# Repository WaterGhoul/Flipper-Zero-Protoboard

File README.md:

# Flipper-Zero-Protoboard
A basic protoboard for the Flipper Zero with LED power indicators

# Purchasing
You can purchase this and my other products on Tindie!

# Donate
Nothing is EVER expected for providing my designs, however if you wish to support my work, you may donate to these addresses.

**ETH** ``0x7C65625d6dac7DC351eEf3C0A21e9f0F4a3B537b``

**BTC** ``bc1q4rn3ceyk42349uuxt2m7mzw4kcewu0e5698fms``

**DOGE** ``DC1Q4ip8mLsAgvbLL4evxJQhaCE7QosFZ9``

**LTC** ``ltc1q33sg6eea2yqzdx85h38v7rpw7kzlgmqtn8m5nm``

# License
<br />This work is licensed under a <a rel="license" href="http://creativecommons.org/licenses/by-sa/4.0/">Creative Commons Attribution-ShareAlike 4.0 International License</a>.

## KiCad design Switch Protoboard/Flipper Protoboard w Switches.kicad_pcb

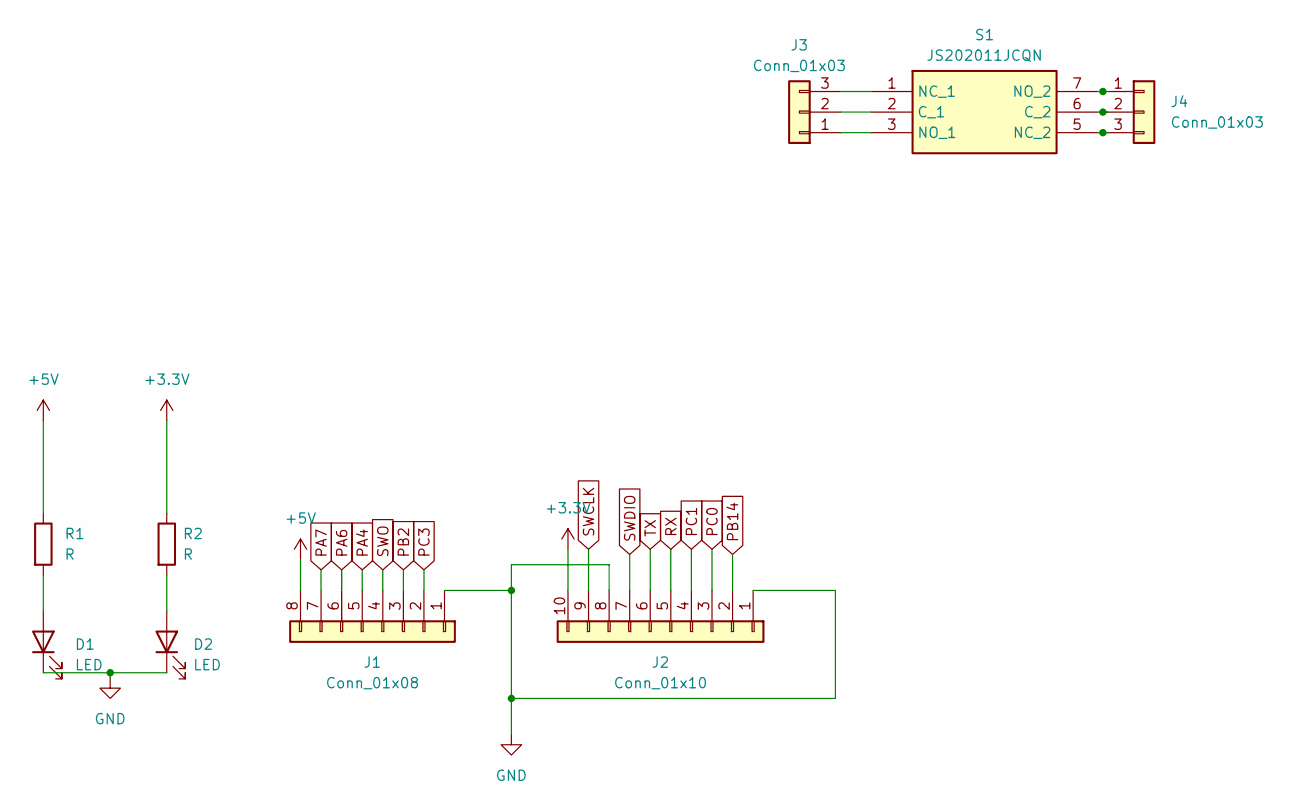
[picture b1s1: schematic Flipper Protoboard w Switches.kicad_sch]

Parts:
D1, D2: LED; LED_0603_1608Metric
J1: Conn_01x08; PinHeader_1x08_P2.54mm_Horizontal
J2: Conn_01x10; PinHeader_1x10_P2.54mm_Horizontal
J3, J4: Conn_01x03; PinHeader_1x03_P2.54mm_Vertical
R1, R2: R; R_0603_1608Metric
S1: JS202011JCQN; Mouser Part Number 611-JS202011JCQN

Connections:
+3.3V: J2.10, R2.1
+5V: J1.8, R1.1
GND: D1.1 (K), D2.1 (K), J1.1, J2.1, J2.8
unnamed: D1.2 (A), R1.2
unnamed: D2.2 (A), R2.2
unnamed: J3.1, S1.3 (NO_1)
unnamed: J3.2, S1.2 (C_1)
unnamed: J3.3, S1.1 (NC_1)
unnamed: J4.1, S1.7 (NO_2)
unnamed: J4.2, S1.6 (C_2)
unnamed: J4.3, S1.5 (NC_2)
PA4: J1.5
PA6: J1.6
PA7: J1.7
PB2: J1.3
PB14: J2.2
PC0: J2.3
PC1: J2.4
PC3: J1.2
RX: J2.5
SWCLK: J2.9
SWDIO: J2.7
SWO: J1.4
TX: J2.6

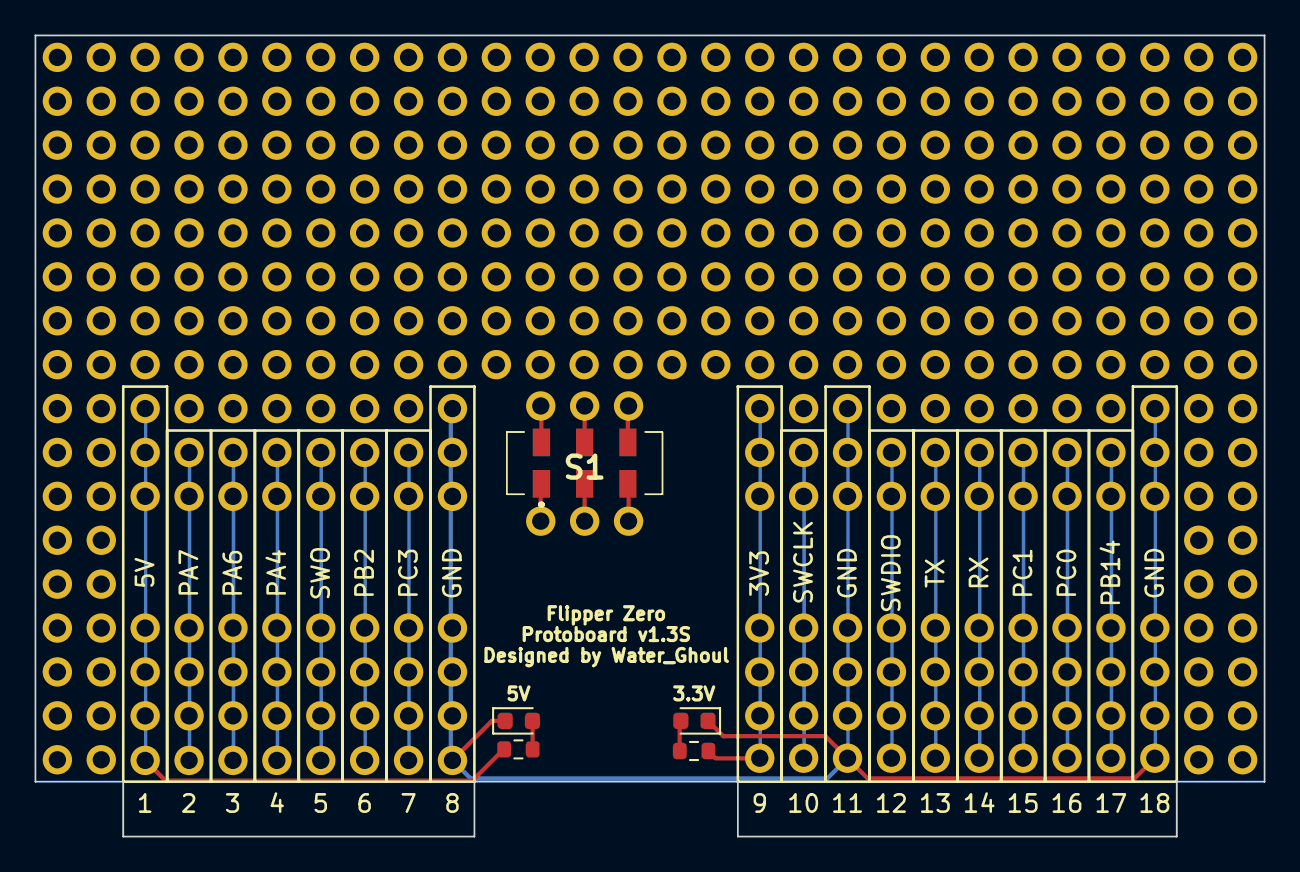
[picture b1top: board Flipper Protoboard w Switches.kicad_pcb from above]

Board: 2 copper layers, 71.1 x 46.4 mm, 377 parts (0 on the bottom side), 11 nets.

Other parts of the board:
REF1, REF1#2, REF2, REF3, REF4, REF5, REF6, REF7, REF8, REF9, REF10, REF11, REF12, REF13, REF14, REF15, REF16, REF17, REF18, REF19, REF20, REF21, REF22, REF23, REF24, REF24#2, REF25, REF26, REF27, REF28, REF29, REF30, REF31, REF32, REF33, REF34, REF35, REF36, REF37, REF38, REF39, REF40, REF41, REF42, REF43, REF44, REF45, REF46, REF47, REF48, REF49, REF50, REF51, REF52, REF53, REF54, REF55, REF56, REF57, REF58, REF59, REF60, REF61, REF62, REF63, REF64, REF65, REF66, REF67, REF68, REF69, REF70, REF71, REF72, REF73, REF74, REF75, REF76, REF77, REF78, REF79, REF80, REF81, REF82, REF83, REF84, REF85, REF86, REF87, REF88, REF89, REF90, REF91, REF92, REF93, REF94, REF95, REF96, REF97, REF98, REF99, REF100, REF101, REF102, REF103, REF104, REF105, REF106, REF107, REF108, REF109, REF110, REF111, REF112, REF113, REF114, REF115, REF116, REF117, REF118, REF119, REF120, REF121, REF121#2, REF122, REF122#2, REF123, REF123#2, REF124, REF124#2, REF125, REF125#2, REF126, REF126#2, REF127, REF127#2, REF128, REF128#2, REF129, REF130, REF131, REF132, REF133, REF134, REF135, REF136, REF137, REF138, REF139, REF140, REF141, REF142, REF143, REF144, REF145, REF146, REF147, REF148, REF149, REF150, REF151, REF152, REF153, REF154, REF155, REF156, REF157, REF158, REF159, REF160, REF161, REF162, REF163, REF164, REF165, REF166, REF167, REF168, REF169, REF169#2, REF170, REF170#2, REF171, REF171#2, REF172, REF172#2, REF173, REF173#2, REF174, REF174#2, REF175, REF175#2, REF176, REF176#2, REF177, REF178, REF179, REF180, REF181, REF182, REF183, REF183#2, REF183#3, REF184, REF184#2, REF184#3, REF185, REF185#2, REF185#3, REF186, REF186#2, REF186#3, REF187, REF187#2, REF187#3, REF188, REF188#2, REF188#3, REF189, REF189#2, REF189#3, REF190, REF190#2, REF190#3, REF191, REF191#2, REF191#3, REF192, REF192#2, REF192#3, REF193, REF194, REF195, REF196, REF197, REF198, REF199, REF200, REF207, REF208, REF209, REF210, REF211, REF212, REF213, REF214, REF215, REF216, REF217, REF218, REF219, REF220, REF221, REF222, REF223, REF224, REF231, REF232, REF233, REF234, REF235, REF236, REF237, REF238, REF239, REF240, REF240#2, REF240#3, REF246, REF247, REF248, REF249, REF250, REF251, REF252, REF253, REF254, REF255, REF256, REF257, REF258, REF259, REF260, REF261, REF262, REF263, REF264, REF265, REF266, REF267, REF268, REF269, REF270, REF271, REF272, REF273, REF274, REF275, REF276, REF277, REF278, REF279, REF280, REF282, REF283, REF285, REF286, REF288, REF289, REF291, REF292, REF294, REF295, REF297, REF298, REF300, REF301, REF303, REF304, REF306, REF307, REF309, REF310, REF312, REF313, REF315, REF316, REF318, REF319, REF321, REF322, REF324, REF325, REF327, REF328, REF330, REF331, REF332, REF333, REF334, REF335, REF336, REF337, REF338, REF339, REF340, REF341, REF342, REF343, REF344, REF345, REF346, REF347, REF348, REF349, REF350, REF351, REF352, REF353, REF354, REF355, REF356, REF357, REF358, REF359, REF360, REF361, REF362: PinSocket_1x01_P2.54mm_Vertical

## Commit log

2023-09-11 Added Source Files
    Added the source KiCAD PCB file and the exported gerbers for manufacturing
2023-09-15 Added new PCB flie
    Added a few minor tweaks to update the board to v1.2
2023-09-17 Added Gerber Files
    Added ZIP files containing Gerber files for both standard and mini sizes of v1.2
2023-09-17 Delete Flipper Protoboard.zip
    Removed old Gerber file ZIP
2023-09-18 Update README.md
    Fixed a minor typo
2023-09-19 Added License
2023-09-20 Fixed 3V3 LED
    Fixed the 3V3 indicator LED grounded to to wrong pin.
2023-09-20 Add files via upload
    Updated gerbers to v1.3
2023-09-26 Added the Switch version
    Uploaded KiCAD files for the version of the protoboard with a built in switch
2023-10-16 Add files via upload
    Added Mini Protoboard v1.4 source file.
